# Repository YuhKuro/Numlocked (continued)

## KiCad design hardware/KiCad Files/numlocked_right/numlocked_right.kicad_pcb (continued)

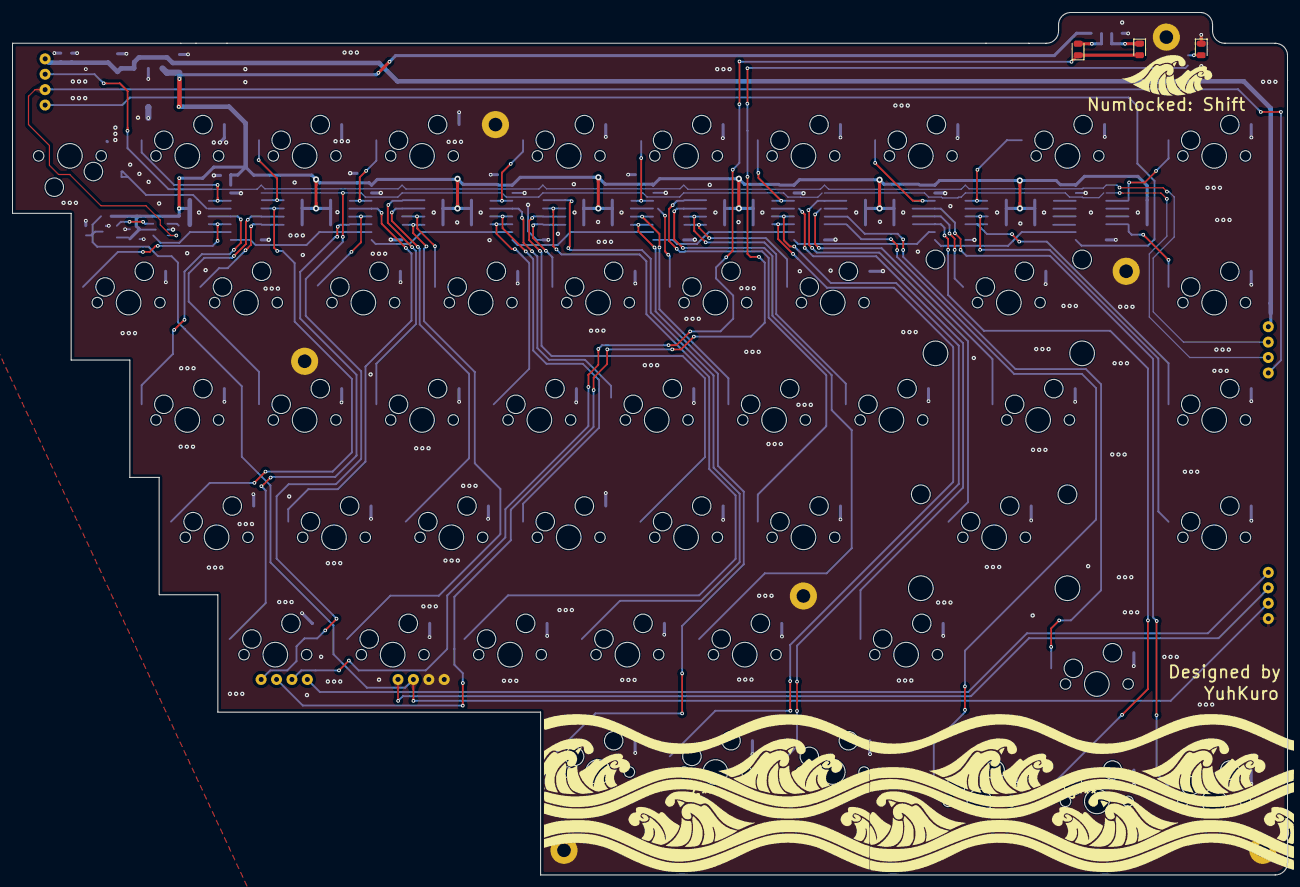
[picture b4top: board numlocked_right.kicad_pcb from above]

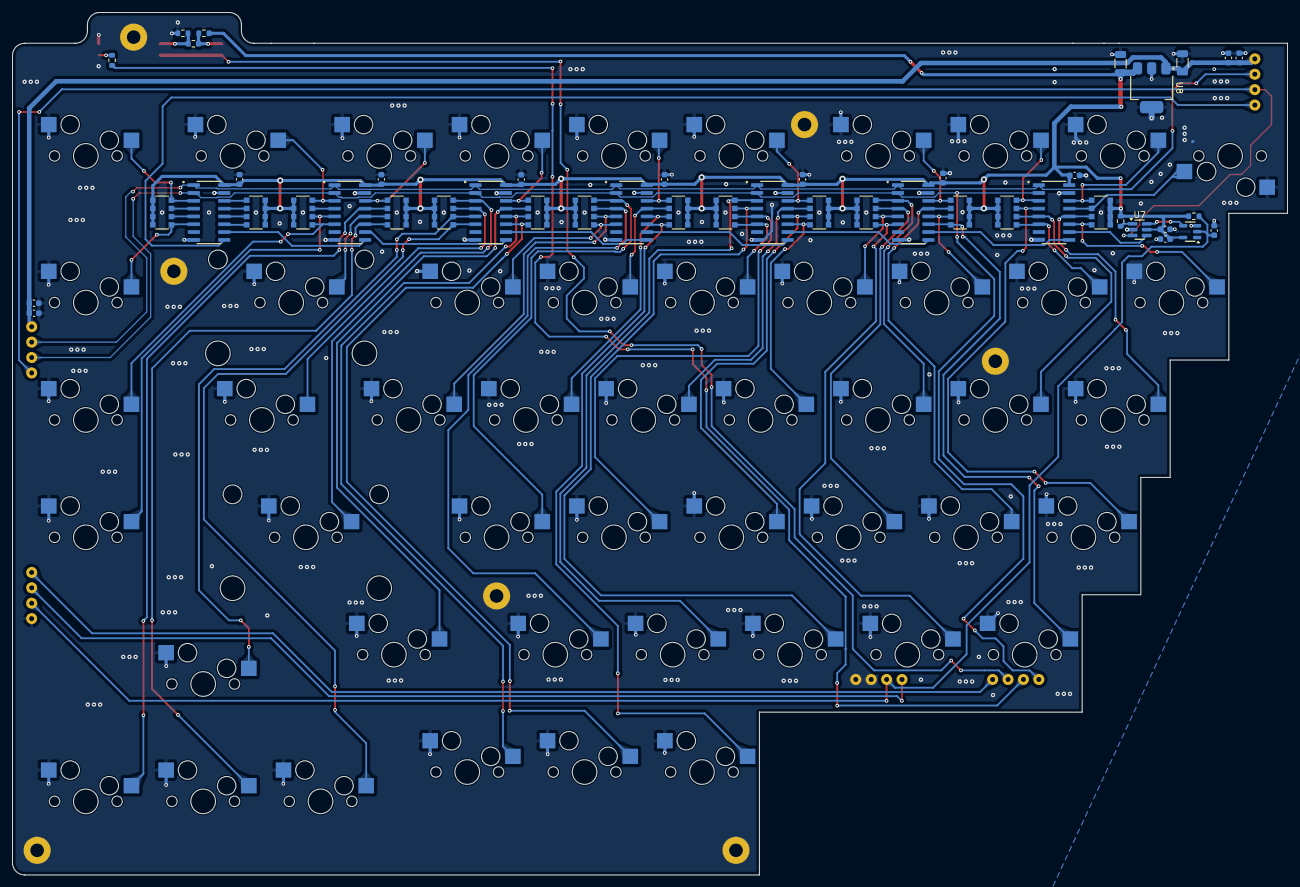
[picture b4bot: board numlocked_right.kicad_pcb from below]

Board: 2 copper layers, 207.0 x 140.0 mm, 110 parts (49 on the bottom side), 80 nets.

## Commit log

2023-05-24 Setting Up.
2023-07-24 Gerber files
2023-07-24 Create gerber
2023-07-24 Moved Files
2023-07-24 Create hubgerber
2023-07-24 Gerbers for HUB
2023-07-27 Create img
2023-07-27 Images of PCB
2023-07-27 Adding Images
2023-07-28 Create File
2023-07-28 Altium Files
2023-08-02 Deleted Old Files.
2023-08-02 Hub PCB
2023-09-11 Create Keyboard
2024-08-17 Finally uploading firmware
2024-08-18 fixed heldkey
2024-08-18 fixed WPM
2024-10-20 game mode
    Added a game mode: ctrl + comma (placeholder shortcut) will disable the windows key.
2024-10-22 Setting up version 2
2024-10-29 Pictures
2024-10-29 fixed readme
2024-10-29 Fixed pictures
2024-10-31 improved images
2024-10-31 fixed pictures v2
2024-11-03 Initial code push for v2
2024-11-07 continuing work on firmware
    prerelease firmware. Board not made yet, so untested. (not even compiled)
2024-11-10 Repo still under maintenance... (housekeeping)
2024-11-11 Working on documentation for Hardware
2024-11-11 formatting test
2024-11-11 fixing formatting
2024-11-17 Continuing documentation
2024-11-17 fixed markdown formatting
2024-11-17 patching more markdown formatting
2024-12-19 initial software push
2024-12-21 Software Alpha 1.0
    - GUI has been created
    - Backend needed
2024-12-22 GUI to Sockets working.
    Python GUI to C Software bridge is done.
    Next step is: Program C background program, connect to keyboard.
2024-12-25 Build instructions
2024-12-25 continuing build instrs
2024-12-29 GUI now has the server, backend is now client.
    Flipped it so that the GUI now posses the server, making the backend lighter in terms of resources.
    Next steps are to implement USB comm, optimize resource usage.
2025-01-06 Fixed socket issues
    Updated so backend can be running 24/7 and the GUI will have no further problems connecting to the backend.
2025-01-06 Super simple timezone conversions. JST seems to be weird?
    I don't think adding/subtracting 9 (or any values) will work as I think its clashing, such as if its at 9 AM + 9 hours = 18 O'Clock and I don't think the C backend accounts for this, so I will have t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
2025-06-24 testing new debouncing. Change to waveform later.
2025-06-26 began adding CDC functionality; will not work right now
2025-06-26 Patched out simple errors, move to CDC+HID
2025-06-26 got rid of all compile errors, next step is to implement CDC protocols.
2025-06-26 setting up cdc 3/10
2025-06-26 Implemented CDC, FIFO, handling protocol. UNTESTED
2025-06-26 began adding boot animation
2025-06-26 Cleaned up warnings, implemented Time functions
2025-06-26 cleanup and time
2025-06-26 Did some cppcheck fixes.
2025-06-27 Implemented USB, Game detection on backend
2025-06-27 Implemented GUI changes surrounding auto game mode
    Enabling game mode manually will automatically toggle off auto game mode in GUI, as well as the back end.
2025-06-27 Finally pushing updated hardware
2025-06-27 Refactored file structure for hardware.
2025-06-27 Readme Changes
2025-07-01 Updated readme with new photos.
2025-07-01 Updated with new photos
2025-07-01 Added hotswap connectors image
2025-07-01 tinkered with layout
2025-07-01 tweaked order
2025-07-01 Added images, changed order, etc.
2025-07-01 uploaded LED picture
2025-07-01 keycap commit
2025-07-02 Changed bmp to pngs for faster loading.
2025-07-02 Optimized Image sizes
2025-07-03 compressed pngs
2025-07-03 quick reade for software
2025-07-04 updated model, updated pictures
2025-07-07 Trying out a gif splash
2025-07-07 Tweaking more readme.
2025-07-07 Github didn't format correctly. reupload.
2025-07-08 Looped Gif
2025-07-08 compressed GIF
2025-07-16 New PCB renders
2025-07-25 Fixed an image I missed earlier.
2025-08-03 Hardware V3 (changing)
2025-08-25 I am stupid. I am stupid
    https://youtu.be/aS4Me48wayM?si=ZLHS1zHPjDahWzTt
    Fixed the dumbest hardware issue known to man.
2025-08-26 Fixed Comments
2025-08-27 firmware work
2025-08-31 firmware weee
2025-09-08 Another quick hardware push. Sorry Github servers.
2025-12-17 fixed rotary encoder, potentially fixed linux issues
